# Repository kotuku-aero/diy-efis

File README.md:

# CanFly Avionics SDK

Open-source SDK for developing custom avionics applications for experimental aircraft. Build once, run on Windows for development and deploy to embedded MIPS32 hardware.

## Table of Contents

- [System Overview](#system-overview)
- [Dual Development Architecture](#dual-development-architecture)
- [Prerequisites](#prerequisites)
- [Quick Start](#quick-start)
- [Project Structure](#project-structure)
- [Building Applications](#building-applications)
  - [Windows Development Build](#windows-development-build)
  - [MIPS32 Embedded Build](#mips32-embedded-build)
- [Application Packaging](#application-packaging)
- [CLion IDE Setup](#clion-ide-setup)
- [Creating Your Own Application](#creating-your-own-application)
- [Troubleshooting](#troubleshooting)

## System Overview

The CanFly SDK provides a complete framework for building glass cockpit avionics applications that run on both Windows (for development/testing) and embedded MIPS32 hardware (for deployment).

**Key Features:**
- **Dual-target compilation:** Same codebase runs on Windows and MIPS32 embedded systems
- **User-mode architecture:** Applications run in protected user space with kernel syscalls
- **Proton UI framework:** XML-based layout system with automatic code generation
- **CanFly syscalls:** Hardware abstraction for CAN bus, sensors, displays, and I/O
- **Automatic packaging:** Post-build packaging creates deployable binary images with SHA256 integrity

## Dual Development Architecture

CanFly applications use a unique dual-target architecture:

### Windows Development Build (MSVC/MinGW)

- **Purpose:** Rapid UI development, testing, and debugging on PC
- **Platform:** Windows 10/11 with Visual Studio or MinGW
- **Libraries:** `w32_canfly.dll` - Windows emulation of CanFly kernel syscalls
- **Output:** Windows executable (`.exe`)
- **Use case:**
  - Develop and test UI layouts
  - Debug application logic
  - Iterate quickly without hardware

### MIPS32 Embedded Build (mips32r2-elf-gcc)

- **Purpose:** Deployment to embedded avionics hardware
- **Platform:** MIPS32 processor running CanFly kernel
- **Libraries:** `canfly` - User-mode syscall stubs
- **Output:**
  - ELF executable (`.elf`) for debugging
  - Packaged binary (`.bin`) with header and SHA256 for deployment
- **Architecture:** User-mode applications running at 0x00000020 in 384KB RAM
- **Use case:**
  - Final deployment to aircraft hardware
  - Hardware integration testing
  - Performance validation

### How It Works

1. **Write once:** Your application code is identical for both targets
2. **Conditional compilation:** `#ifdef MIPS32_BUILD` for platform-specific code
3. **Common syscalls:** CanFly API is the same on both platforms
4. **Build twice:**
   - Windows build for development
   - MIPS32 build for deployment

## Prerequisites

### For Windows Development (Required)

**Recommended IDE:**
- **CLion** (free for non-commercial use): https://www.jetbrains.com/clion/
  - Excellent CMake integration
  - Cross-platform debugging
  - Built-in code analysis

**Build Tools (choose one):**

**Option 1: Visual Studio 2022 Build Tools** (recommended)
```powershell
# Run as Administrator
winget install Microsoft.VisualStudio.2022.BuildTools --force --override "--passive --wait --add Microsoft.VisualStudio.Workload.VCTools;includeRecommended"
```

**Option 2: MinGW-w32** (alternative)
```powershell
winget install mingw-w32
```

**Additional Tools:**
- CMake 3.15+ (bundled with CLion)
- Git with submodules support
- Python 3.8+ (for build tools and packaging)

### For MIPS32 Embedded Development (Required)

**MIPS32 Compiler Toolchain:**
- Download from: https://github.com/kotuku-aero/mips32
- Extract to: `C:\pic32\` (or update toolchain file path)
- Adds: `mips32r2-elf-gcc`, `mips32r2-elf-ld`, `mips32r2-elf-size`, `mips32r2-elf-gdb`

**Python Libraries:**
```bash
pip install pyelftools
```

### Not Supported

**XC32 Compiler:** While the codebase can build with XC32, we do not officially support it. Use the free mips32r2-elf-gcc toolchain instead.

## Quick Start

### 1. Clone the Repository

```bash
git clone --recurse-submodules https://github.com/kotuku-aero/canfly.git
cd canfly/diy-efis
```

### 2. Build Example Application (Windows)

```bash
cd apps/att_au_nz
mkdir build-win
cd build-win
cmake ..
cmake --build . --config Release

# Run the application
./bin/Release/att_au_nz.exe -x 1024 -y 768
```

### 3. Build for MIPS32 Hardware

```bash
cd apps/att_au_nz
mkdir build-mips32
cd build-mips32
cmake -DCMAKE_TOOLCHAIN_FILE=../../cmake/pic32-mips32r2-toolchain.cmake ..
cmake --build .

# Outputs:
# - firmware/att_au_nz.elf (for debugging)
# - images/att_au_nz.bin (for deployment)
```

## Project Structure

```
diy-efis/
├── apps/                      # User applications
│   ├── att_au_nz/            # Example: Attitude indicator (AU/NZ regs)
│   │   ├── main.c            # Application entry point
│   │   ├── att.c             # Attitude display logic
│   │   ├── layout/           # XML UI layouts
│   │   └── CMakeLists.txt
│   └── [your_app]/           # Your custom application
|
├── bin/                      # binary files
|   ├── CanFly.Commander.exe  # CanFly application manager
|   └── msh.exe               # gdb server for canfly hardware.
│
├── src/                      # SDK source code
│   ├── canfly/               # User-mode kernel interface
│   │   ├── canfly_stubs.c    # Syscall stubs (generated)
│   │   ├── newlib_stubs.c    # Minimal C library support
│   │   ├── crt0.S            # User-mode startup code
│   │   └── canfly_app.ld     # Linker script (384KB user RAM)
│   ├── mfdlib/               # Display/UI library
│   └── proton/               # UI framework & XML processing
|
├── tools/                    # Development tools
|   └── yehudi                # XML layout code generator
│
├── lib/                      # Platform abstraction
│   ├── libw32_canfly.so      # linux version (for development)
|   └── w32_canfly.dll/lib    # Windows DLL export definitions
│
├── cmake/                    # Build system
│   ├── MFDCommon.cmake       # Shared build configuration
│   └── mips32-toolchain.cmake
│
├── scripts/                  # Build tools
│   └── package_usermode.py   # Binary packaging tool
│
└── include/                  # SDK headers
    ├── canfly_api.md         # API documentation
    ├── canfly_types.h        # Common types
    ├── CanFlyID.def          # Definitions of the published CAN IDs
    ├── canfly.h              # Main CanFly API
    └── sys_canfly.h          # Syscall definitions
```

## Building Applications

### Windows Development Build

Used for rapid development and testing without hardware.

**From CLion:**
1. Open `diy-efis` as project
2. Select **Windows-Release** profile
3. Build → Build Project (Ctrl+F9)
4. Run → Run (Shift+F10)

**From Command Line:**
```bash
cd apps/att_au_nz
cmake -B build-win -DCMAKE_BUILD_TYPE=Release
cmake --build build-win --config Release

# Run with custom window size
./build-win/bin/Release/att_au_nz.exe -x 1024 -y 768
```

**Debug Build:**
```bash
cmake -B build-win-debug -DCMAKE_BUILD_TYPE=Debug
cmake --build build-win-debug --config Debug
```

### MIPS32 Embedded Build

Used for deployment to avionics hardware.

**From CLion:**
1. Select **MIPS32-Release** profile
2. Build → Build Project (Ctrl+F9)
3. Output:
   - `cmake-build-mips32-release/firmware/att_au_nz.elf`
   - `cmake-build-mips32-release/images/att_au_nz.bin`

**From Command Line:**
```bash
cd apps/att_au_nz
cmake -B build-mips32 \
  -DCMAKE_TOOLCHAIN_FILE=../../cmake/pic32-mips32r2-toolchain.cmake \
  -DCMAKE_BUILD_TYPE=Release
cmake --build build-mips32

# View program size
mips32r2-elf-size build-mips32/firmware/att_au_nz.elf
```

**Build Output:**
```
firmware/att_au_nz.elf    # ELF file with debug symbols
images/att_au_nz.bin      # Packaged binary for deployment
```

## Application Packaging

MIPS32 builds automatically package the ELF into a deployable binary format.

### Package Format

```
[32-byte header]
  - 0x10000008: Branch instruction (skip header)
  - 0x00000c00: EHB (execution hazard barrier)
  - Image length (big-endian)
  - Reserved
  - Image name (16 bytes)

[Application binary]
  - Code and data sections from ELF
  - 32-byte aligned

[SHA256 signature]
  - "sig-sha256" (28 bytes)
  - Hash length: 32 (big-endian)
  - SHA256 hash of header + binary
  - Padding to 32-byte alignment
```

### Manual Packaging

```bash
python3 scripts/package_usermode.py \
  -e firmware/att_au_nz.elf \
  -o images \
  -n att_au_nz
```

### Deployment

Upload the `.bin` file to the CanFly device using the Commander tool:
1. Open Commander (.NET tool)
2. File Explorer → Upload
3. Select `att_au_nz.bin`
4. Device loads and verifies SHA256
5. Application runs in user-mode at 0x00000020

Keep the `.elf` file for debugging with GDB/JTAG.

## CLion IDE Setup

CLion is the recommended IDE for CanFly development.

### Install CLion

Download from: https://www.jetbrains.com/clion/

**Free License Options:**
- Educational license (students/teachers)
- Open source project license
- 30-day trial

### CMake Profiles

Create these profiles in: **Settings → Build, Execution, Deployment → CMake**

#### Profile: Windows-Debug
```
Name: Windows-Debug
Build type: Debug
Toolchain: Visual Studio (or MinGW)
CMake options: (leave empty)
Build directory: cmake-build-debug
```

#### Profile: Windows-Release
```
Name: Windows-Release
Build type: Release
Toolchain: Visual Studio (or MinGW)
CMake options: (leave empty)
Build directory: cmake-build-release
```

#### Profile: MIPS32-Debug
```
Name: MIPS32-Debug
Build type: Debug
Toolchain: Visual Studio (placeholder - actual toolchain from file)
CMake options: -DCMAKE_TOOLCHAIN_FILE=cmake/pic32-mips32r2-toolchain.cmake
Build directory: cmake-build-mips32-debug
```

#### Profile: MIPS32-Release
```
Name: MIPS32-Release
Build type: Release
Toolchain: Visual Studio (placeholder - actual toolchain from file)
CMake options: -DCMAKE_TOOLCHAIN_FILE=cmake/pic32-mips32r2-toolchain.cmake
Build directory: cmake-build-mips32-release
```

### Building in CLion

1. **Select Profile:** Bottom toolbar → Profile dropdown
2. **Build All:** Hammer icon or Ctrl+F9
3. **Build Target:** Right-click target → Build
4. **Clean:** Build → Clean
5. **Reload CMake:** Tools → CMake → Reload CMake Project

### Debugging

**Windows Builds:**
- Set breakpoints in source
- Select Windows-Debug profile
- Run → Debug (Shift+F9)
- Full debugging support

**MIPS32 Builds:**
- Use `.elf` file with GDB
- Create an Embedded debug target in CLion
- CLion will download the application into the device and start debugging

## Creating Your Own Application

### 1. Create Application Directory

```bash
cd diy-efis/apps
mkdir my_avionics
cd my_avionics
```

### 2. Create CMakeLists.txt

```cmake
cmake_minimum_required(VERSION 3.15)
project(my_avionics C)

# Include common configuration
include(${CMAKE_CURRENT_SOURCE_DIR}/../../cmake/MFDCommon.cmake)

# Source files
set(SOURCES
    main.c
    my_logic.c
)

# Platform-specific build
if(MIPS32_BUILD)
    # MIPS32 embedded build
    add_executable(my_avionics ${SOURCES})

    mfd_configure_pic32_target(
        TARGET my_avionics
    )
else()
    # Windows development build
    add_executable(my_avionics ${SOURCES})

    mfd_configure_win32_target(
        TARGET my_avionics
    )
endif()
```

### 3. Create main.c

```c
#include "canfly.h"

#ifndef MIPS32_BUILD
// Windows debug arguments
int main(int argc, char** argv)
  {
  if (failed(canfly_init(argc, argv)))
    return -1;
#else
// MIPS32 user-mode (no arguments)
int main()
  {
#endif

  // Your application logic here

  return 0;
  }
```

### 4. Build and Test

```bash
# Windows build
cmake -B build-win
cmake --build build-win

# MIPS32 build
cmake -B build-mips32 \
  -DCMAKE_TOOLCHAIN_FILE=../../cmake/pic32-mips32r2-toolchain.cmake
cmake --build build-mips32
```

## Troubleshooting

### MIPS32 Compiler Not Found

**Error:** `CMAKE_C_COMPILER not found`

**Solution:**
```bash
# Verify installation
C:\pic32\bin\mips32r2-elf-gcc.exe --version

# Update toolchain file if installed elsewhere
# Edit: cmake/pic32-mips32r2-toolchain.cmake
set(MIPS32_TOOLCHAIN_PATH "C:/your/path/here")
```

### Missing Python Dependencies

**Error:** `ModuleNotFoundError: No module named 'elftools'`

**Solution:**
```bash
pip install pyelftools
```

### Linker Errors: Undefined Reference to Syscalls

**Error:** `undefined reference to 'cfg_open_key'`

**Solution:**
- Ensure `canfly` library is linked (should be automatic via `MFDCommon.cmake`)
- Check link order in `mfd_configure_pic32_target()`
- Verify syscall stubs are generated: `diy-efis/src/canfly/canfly_stubs.c`

### Entry Point Not Found

**Error:** `warning: cannot find entry symbol _reset`

**Solution:**
- Ensure `crt0.S` is in `canfly` library sources
- Verify CMake project includes ASM language: `project(canfly LANGUAGES C ASM)`
- Check linker script: `canfly_app.ld` defines `ENTRY(_reset)`

### Program Size Too Small (24 bytes)

**Issue:** Binary is suspiciously small, likely missing code

**Solution:**
- Check that `canfly` library links before `gcc` in link order
- Verify all source files are in `add_executable()` or linked libraries
- Look for undefined symbols in build output

### CLion Shows Red Underlines

**Issue:** Code appears to have errors but builds successfully

**Solution:**
1. Tools → CMake → Reset Cache and Reload Project
2. Ensure correct CMake profile is selected
3. File → Invalidate Caches → Invalidate and Restart

### Windows Build Can't Find w32_canfly.lib

**Error:** `Cannot find w32_canfly.lib`

**Solution:**
- Ensure submodules are initialized: `git submodule update --init --recursive`
- Check that `libs/w32_canfly/` exists and contains the library
- Verify path in `mfd_configure_win32_target()` function

## Additional Resources

- **CanFly Kernel Documentation:** [Coming soon]
- **Proton UI Framework Guide:** See `src/proton/README.md`
- **MIPS32 Toolchain:** https://github.com/kotuku-aero/mips32r2-elf-gcc
- **CMake Documentation:** https://cmake.org/documentation/
- **CLion CMake Support:** https://www.jetbrains.com/help/clion/cmake-support.html

## Contributing

Contributions are welcome! Please:
1. Fork the repository
2. Create a feature branch
3. Test on both Windows and MIPS32
4. Submit a pull request

## License

[Your license here]

## Support

For questions or issues:
- GitHub Issues: https://github.com/kotuku-aero/canfly/issues
- Email: support@kotuku.aero
- Forum: [Coming soon]

---

**Happy flying with CanFly!** ✈️

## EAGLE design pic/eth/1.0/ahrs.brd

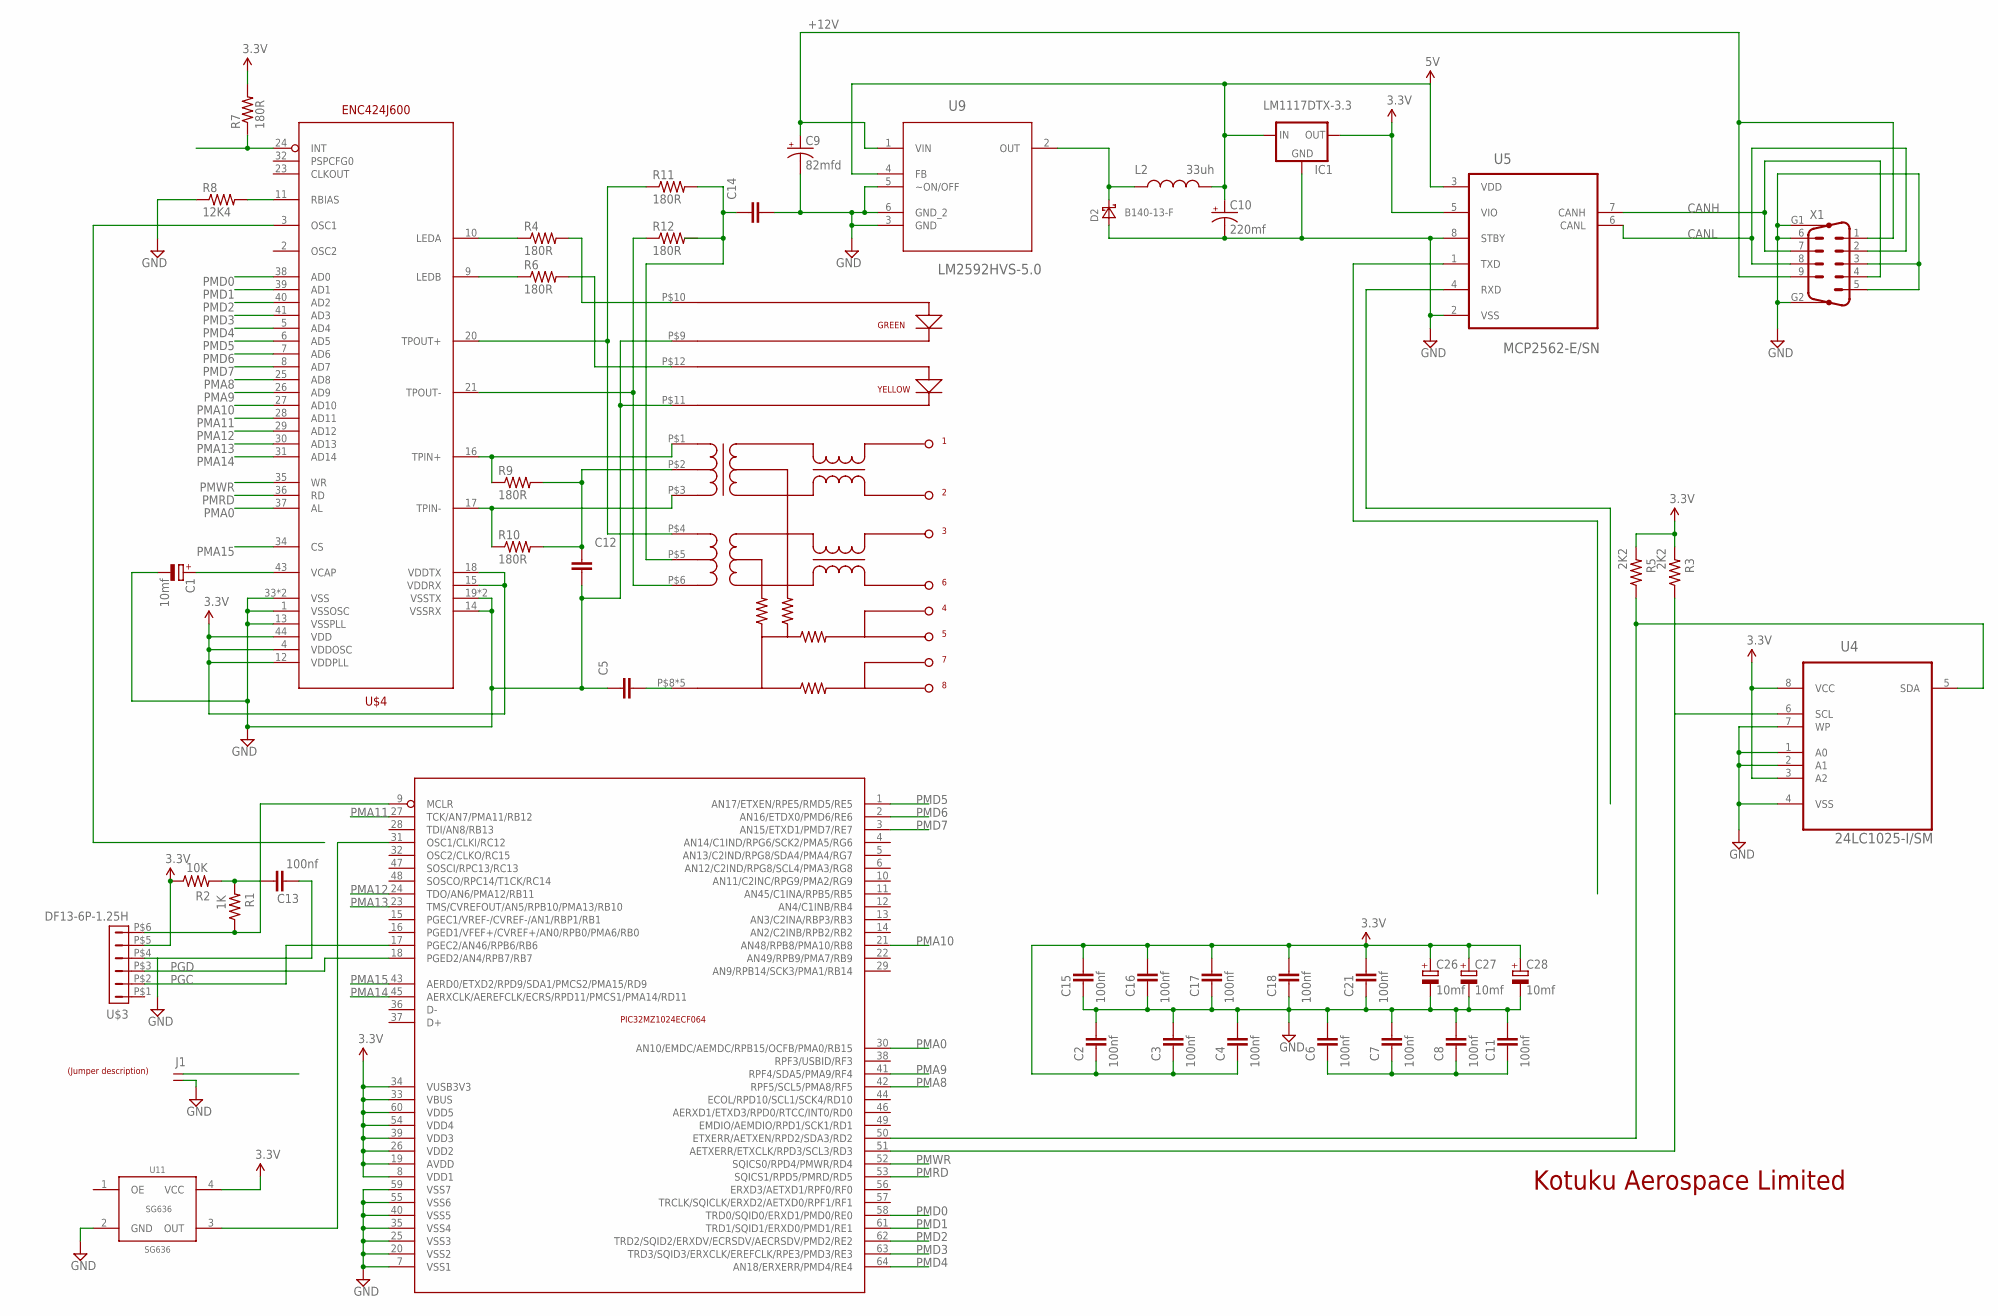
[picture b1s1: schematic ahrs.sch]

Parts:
C1, C26, C27, C28: 10mf; SMC_A
C2, C3, C4, C6, C7, C8, C11, C13, C15, C16, C17, C18, C21: 100nf; C805
C5: CAPACITOR_NPOL-1206; C1206
C9: 82mfd; SVPF-E7
C10: 220mf; EIA7343
C12, C14: CAPACITOR_NPOL-0603; C603
D2: B140-13-F; SMA
IC1: LM1117DTX-3.3; TO252
J1: JUMPER-1X2
L2: 33uh; 1812
R1: 1K; 0603-RES; PARTNO ERJ-3GEYJ103V
R2: 10K; 0603-RES; PARTNO ERJ-3GEYJ103V
R3, R5: 2K2; 0603-RES; PARTNO ERJ-3GEYJ103V
R4, R6, R7, R9, R10, R11, R12: 180R; 0603-RES
R8: 12K4; 0603-RES
U4: 24LC1025-I/SM; SOIC8-N_MC
U5: MCP2562-E/SN; SOIC-8N
U9: LM2592HVS-5.0; TO170P1435X457-5N
U11: SG636; PARTNO SG-636PCE 10.000MHZ
U$1: LABEL_JUMPER_1X2; JUMP2_DESC
U$2: PIC32MZ1024; TQFP-64
U$3: DF13-6P-1.25H; DF13A-6P-1.25H
U$4: ENC424J600; TQFP44
U$5: J1B1211CCD
X1: M09HP

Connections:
3.3V: C2.2, C3.2, C4.2, C15.1, C16.1, C17.1, C18.1, C21.1, C26.+, C27.+, C28.+, IC1.TAB (OUT), R2.1, R3.2, R5.2, R7.2, U4.3 (A2), U4.8 (VCC), U5.5 (VIO), U11.4 (VCC), U$2.8 (VDD1), U$2.19 (AVDD), U$2.26 (VDD2), U$2.33 (VBUS), U$2.34 (VUSB3V3), U$2.39 (VDD3), U$2.54 (VDD4), U$2.60 (VDD5), U$3.P$5 (5), U$4.4 (VDDOSC), U$4.12 (VDDPLL), U$4.15 (VDDRX), U$4.18 (VDDTX), U$4.44 (VDD)
5V: C10.A (+), IC1.2 (IN), L2.2, U5.3 (VDD), U9.4 (FB)
!MCLR: R1.1, U$2.9 (MCLR), U$3.P$6 (6)
+12V: C9.P$2 (+), U9.1 (VIN), X1.1, X1.9
CANH: U5.7 (CANH), X1.4, X1.7
CANL: U5.6 (CANL), X1.2, X1.8
GND: C1.-, C2.1, C3.1, C4.1, C5.1, C6.1, C7.1, C8.1, C9.P$1 (-), C10.C (-), C11.1, C12.2, C13.2, C14.2, C15.2, C16.2, C17.2, C18.2, C21.2, C26.-, C27.-, C28.-, D2.A, IC1.1 (GND), J1.2, R8.1, U4.1 (A0), U4.2 (A1), U4.4 (VSS), U4.7 (WP), U5.2 (VSS), U5.8 (STBY), U9.3 (GND), U9.5 (~ON/OFF), U9.6 (GND_2), U11.2 (GND), U$2.7 (VSS1), U$2.20 (VSS2), U$2.25 (VSS3), U$2.35 (VSS4), U$2.40 (VSS5), U$2.55 (VSS6), U$2.59 (VSS7), U$3.P$4 (4), U$4.1 (VSSOSC), U$4.13 (VSSPLL), U$4.14 (VSSRX), U$4.19 (VSSTX), U$4.22 (VSSTX), U$4.33 (VSS), U$4.42 (VSS), U$5.P$9 (GREEN_K), U$5.P$11 (YELLOW_K), X1.3, X1.5, X1.6, X1.G1, X1.G2
unnamed: R11.1, U$4.20 (TPOUT+), U$5.P$4 (RX+)
unnamed: R12.1, U$4.21 (TPOUT-), U$5.P$6 (RX-)
unnamed: R9.1, U$4.16 (TPIN+), U$5.P$1 (TX+)
unnamed: C13.1, R1.2, R2.2
unnamed: R10.1, U$4.17 (TPIN-), U$5.P$3 (TX-)
unnamed: U11.3 (OUT), U$2.31 (OSC1/CLKI/RC12)
unnamed: C6.2, C7.2, C8.2, C11.2
unnamed: R4.1, U$4.10 (LEDA)
unnamed: R4.2, U$5.P$10 (GREEN_A)
unnamed: D2.C, L2.1, U9.2 (OUT)
unnamed: R6.2, U$5.P$12 (YELLOW_A)
unnamed: R6.1, U$4.9 (LEDB)
unnamed: R7.1, U$4.24 (INT)
unnamed: R8.2, U$4.11 (RBIAS)
unnamed: C5.2, U$5.P$8 (GNDIN), U$5.P$13 (GNDIN), U$5.P$14 (GNDIN), U$5.P$15 (GNDIN), U$5.P$16 (GNDIN)
unnamed: C1.+, U$4.43 (VCAP)
unnamed: C12.1, R9.2, R10.2, U$5.P$2 (P2IN)
unnamed: C14.1, R11.2, U$5.P$5 (P5IN)
PGC: U$2.17 (PGEC2/AN46/RPB6/RB6), U$3.P$2 (2)
PGD: U$2.18 (PGED2/AN4/RPB7/RB7), U$3.P$3 (3)
PMA0: U$2.30 (AN10/EMDC/AEMDC/RPB15/OCFB/PMA0/RB15), U$4.37 (AL)
PMA8: U$2.42 (RPF5/SCL5/PMA8/RF5), U$4.25 (AD8)
PMA9: U$2.41 (RPF4/SDA5/PMA9/RF4), U$4.26 (AD9)
PMA10: U$2.21 (AN48/RPB8/PMA10/RB8), U$4.27 (AD10)
PMA11: U$2.27 (TCK/AN7/PMA11/RB12), U$4.28 (AD11)
PMA12: U$2.24 (TDO/AN6/PMA12/RB11), U$4.29 (AD12)
PMA13: U$2.23 (TMS/CVREFOUT/AN5/RPB10/PMA13/RB10), U$4.30 (AD13)
PMA14: U$2.45 (AERXCLK/AEREFCLK/ECRS/RPD11/PMCS1/PMA14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), U$4.31 (AD14)
PMA15: U$2.43 (AERD0/ETXD2/RPD9/SDA1/PMCS2/PMA15/RD9), U$4.34 (CS)
PMD0: U$2.58 (TRD0/SQID0/ERXD1/PMD0/RE0), U$4.38 (AD0)
PMD1: U$2.61 (TRD1/SQID1/ERXD0/PMD1/RE1), U$4.39 (AD1)
PMD2: U$2.62 (TRD2/SQID2/ERXDV/ECRSDV/AECRSDV/PMD2/RE2), U$4.40 (AD2)
PMD3: U$2.63 (TRD3/SQID3/ERXCLK/EREFCLK/RPE3/PMD3/RE3), U$4.41 (AD3)
PMD4: U$2.64 (AN18/ERXERR/PMD4/RE4), U$4.5 (AD4)
PMD5: U$2.1 (AN17/ETXEN/RPE5/RMD5/RE5), U$4.6 (AD5)
PMD6: U$2.2 (AN16/ETDX0/PMD6/RE6), U$4.7 (AD6)
PMD7: U$2.3 (AN15/ETXD1/PMD7/RE7), U$4.8 (AD7)
PMRD: U$2.53 (SQICS1/RPD5/PMRD/RD5), U$4.36 (RD)
PMWR: U$2.52 (SQICS0/RPD4/PMWR/RD4), U$4.35 (WR)
SCL: R3.1, U4.6 (SCL), U$2.51 (AETXERR/ETXCLK/RPD3/SCL3/RD3)
SDA: R5.1, U4.5 (SDA), U$2.50 (ETXERR/AETXEN/RPD2/SDA3/RD2)

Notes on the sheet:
Kotuku Aerospace Limited

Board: 2 copper layers, 48 parts (0 on the bottom side), 48 nets, no tracks yet.

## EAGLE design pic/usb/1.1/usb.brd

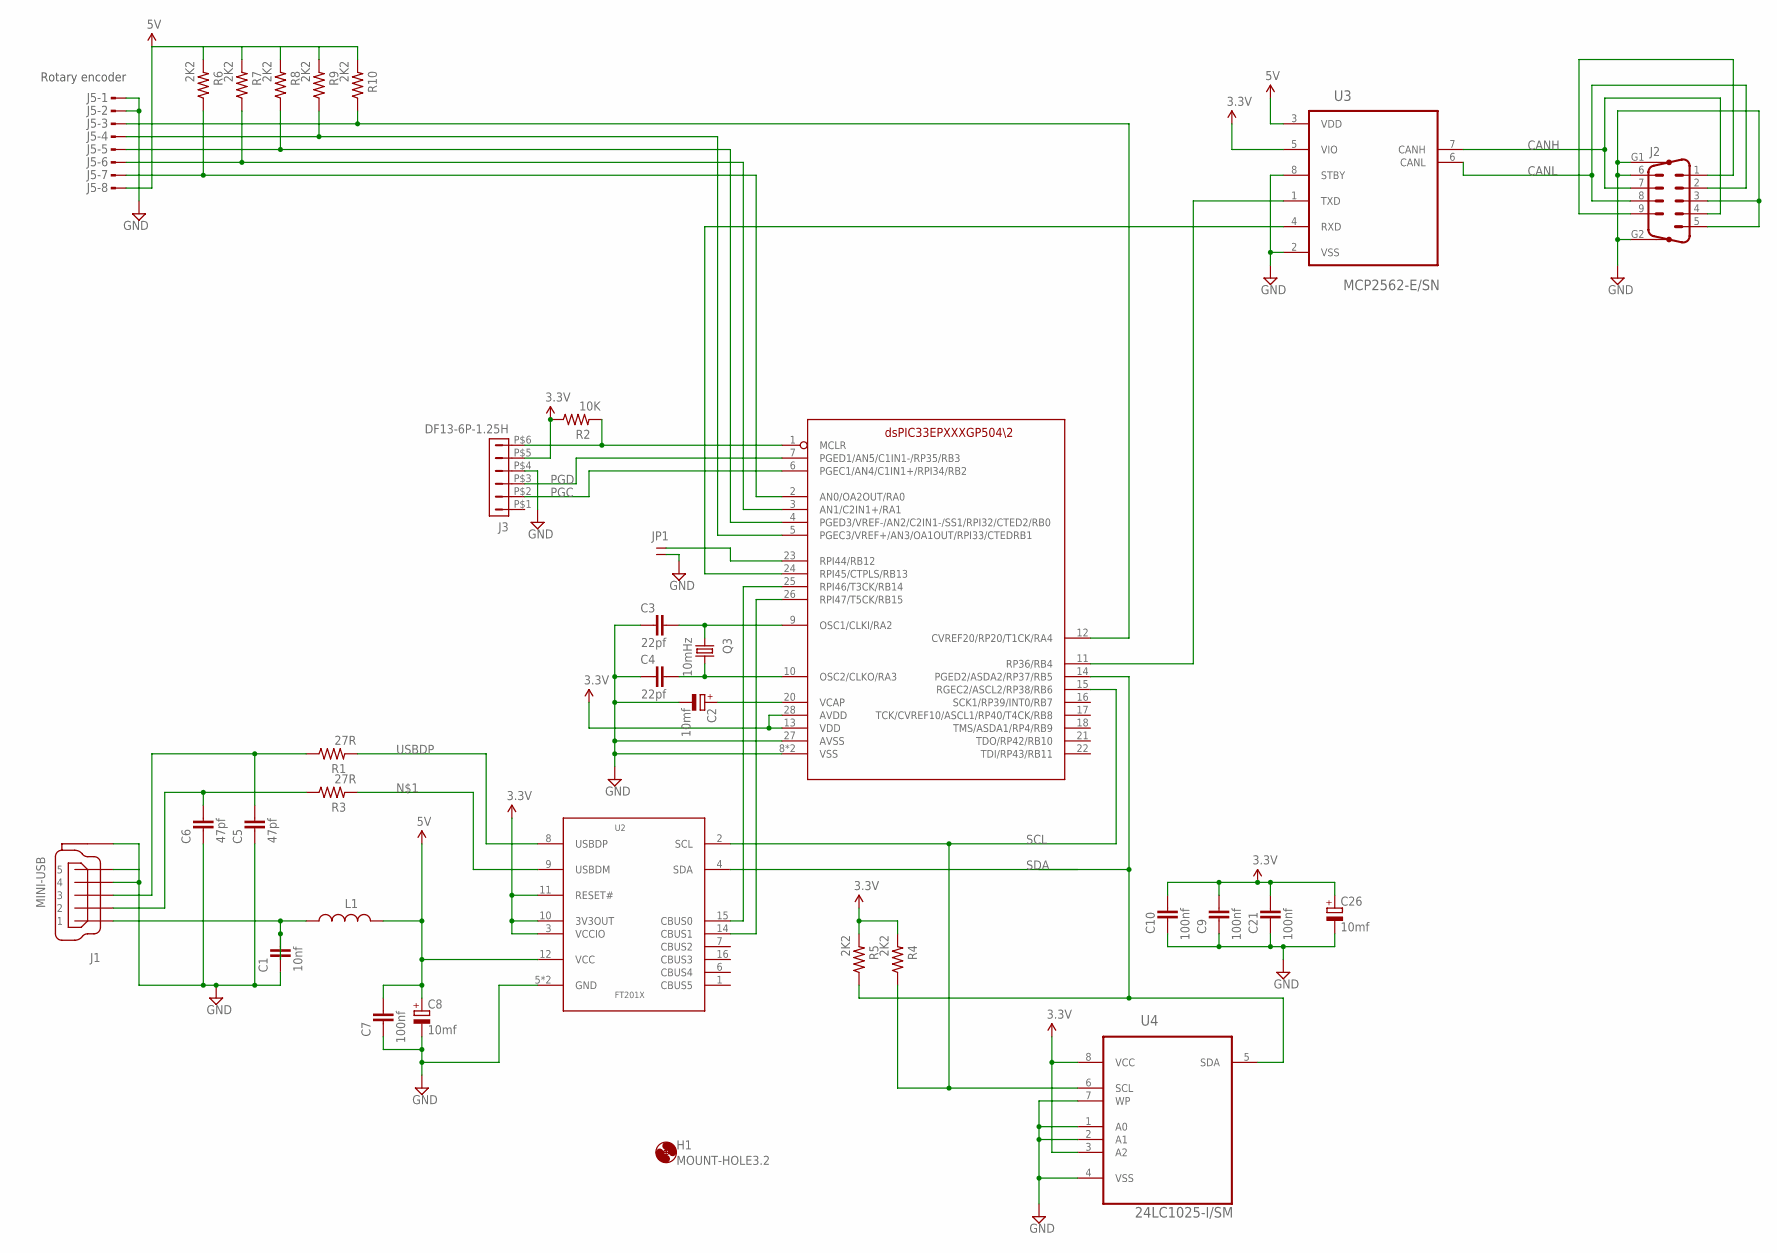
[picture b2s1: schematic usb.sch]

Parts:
C1: 10nf; C805
C2, C8, C26: 10mf; SMC_A
C3, C4: 22pf; C805
C5, C6: 47pf; C805
C7, C9, C10, C21: 100nf; C805
H1: MOUNT-HOLE3.2; 3,2
J1: MINI-USB
J2: M09HP
J3: DF13-6P-1.25H; DF13A-6P-1.25H
J5: MTOP-8; PARTNO 7-215079-8
JP1: JUMPER-1X2
L1: FERRITE-0603; FB603
Q3: 10mHz; HC49/S; PARTNO 9B-10.000MBBK-B
R1, R3: 27R; 0603-RES; PARTNO ERJ-3GEYJ103V
R2: 10K; 0603-RES; PARTNO ERJ-3GEYJ103V
R4, R5: 2K2; 0603-RES; PARTNO ERJ-3GEYJ103V
R6, R7, R8, R9, R10: 2K2; 0603-RES; PARTNO RC0603FR-072K2L
U1: DSPIC33EPXXXGP502; SOIC-28
U2: FT201X; TSSOP-16
U3: MCP2562-E/SN; SOIC-8N
U4: 24LC1025-I/SM; SOIC8-N_MC

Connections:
3.3V: C9.1, C10.1, C21.1, C26.+, J3.P$5 (5), R2.1, R4.2, R5.2, U1.13 (VDD), U1.28 (AVDD), U2.3 (VCCIO), U2.10 (3V3OUT), U2.11 (RESET#), U3.5 (VIO), U4.3 (A2), U4.8 (VCC)
5V: C7.1, C8.+, J5.8, L1.2, R6.2, R7.2, R8.2, R9.2, R10.2, U2.12 (VCC), U3.3 (VDD)
!MCLR: J3.P$6 (6), R2.2, U1.1 (MCLR)
+12V: J2.1, J2.9
A+: J5.7, R6.1, U1.2 (AN0/OA2OUT/RA0)
A-: J5.6, R7.1, U1.3 (AN1/C2IN1+/RA1)
B+: J5.5, R8.1, U1.4 (PGED3/VREF-/AN2/C2IN1-/SS1/RPI32/CTED2/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)
B-: J5.4, R9.1, U1.5 (PGEC3/VREF+/AN3/OA1OUT/RPI33/CTEDRB1)
CANH: J2.4, J2.7, U3.7 (CANH)
CANL: J2.2, J2.8, U3.6 (CANL)
GND: C1.2, C2.-, C3.2, C4.2, C5.2, C6.2, C7.2, C8.-, C9.2, C10.2, C21.2, C26.-, J1.4, J1.5, J1.M1 (MOUNT), J1.M2 (MOUNT), J1.M3 (MOUNT), J1.M4 (MOUNT), J2.3, J2.5, J2.6, J2.G1, J2.G2, J3.P$4 (4), J5.1, J5.2, JP1.2, U1.8 (VSS), U1.19 (VSS), U1.27 (AVSS), U2.5 (GND), U2.13 (GND), U3.2 (VSS), U3.8 (STBY), U4.1 (A0), U4.2 (A1), U4.4 (VSS), U4.7 (WP)
unnamed: R3.2, U2.9 (USBDM)
unnamed: U1.25 (RPI46/T3CK/RB14), U2.15 (CBUS0)
unnamed: U1.24 (RPI45/CTPLS/RB13), U3.4 (RXD)
unnamed: C2.+, U1.20 (VCAP)
unnamed: C3.1, Q3.2, U1.9 (OSC1/CLKI/RA2)
unnamed: U1.11 (RP36/RB4), U3.1 (TXD)
unnamed: U1.26 (RPI47/T5CK/RB15), U2.14 (CBUS1)
unnamed: C6.1, J1.2, R3.1
unnamed: C1.1, J1.1, L1.1
unnamed: C5.1, J1.3, R1.1
unnamed: JP1.1, U1.23 (RPI44/RB12)
unnamed: C4.1, Q3.1, U1.10 (OSC2/CLKO/RA3)
PGC: J3.P$2 (2), U1.6 (PGEC1/AN4/C1IN1+/RPI34/RB2)
PGD: J3.P$3 (3), U1.7 (PGED1/AN5/C1IN1-/RP35/RB3)
SCL: R4.1, U1.15 (RGEC2/ASCL2/RP38/RB6), U2.2 (SCL), U4.6 (SCL)
SDA: R5.1, U1.14 (PGED2/ASDA2/RP37/RB5), U2.4 (SDA), U4.5 (SDA)
SW1: J5.3, R10.1, U1.12 (CVREF20/RP20/T1CK/RA4)
USBDP: R1.2, U2.8 (USBDP)

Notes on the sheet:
Rotary encoder

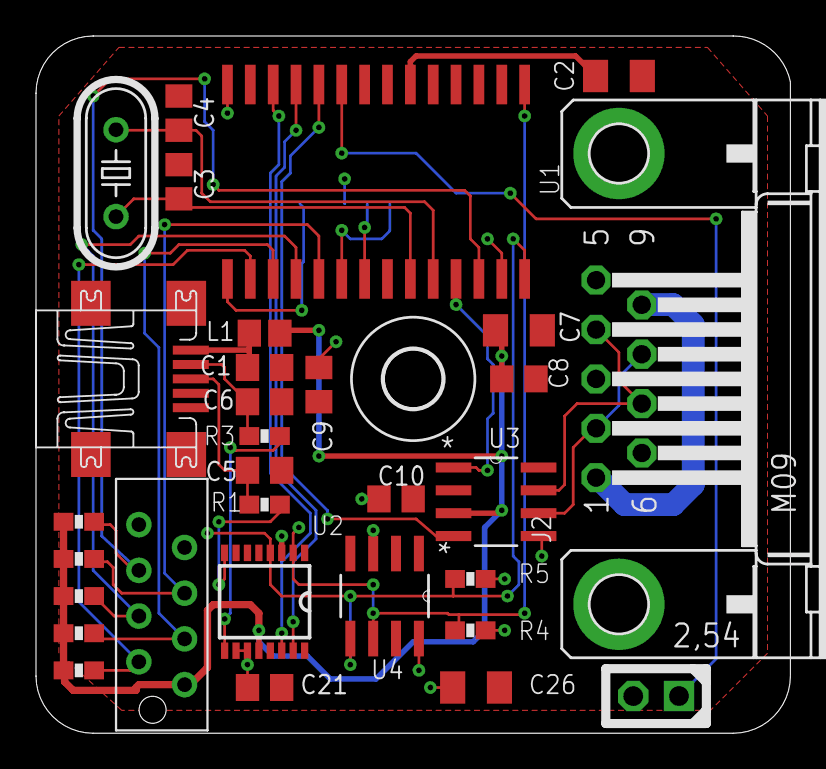
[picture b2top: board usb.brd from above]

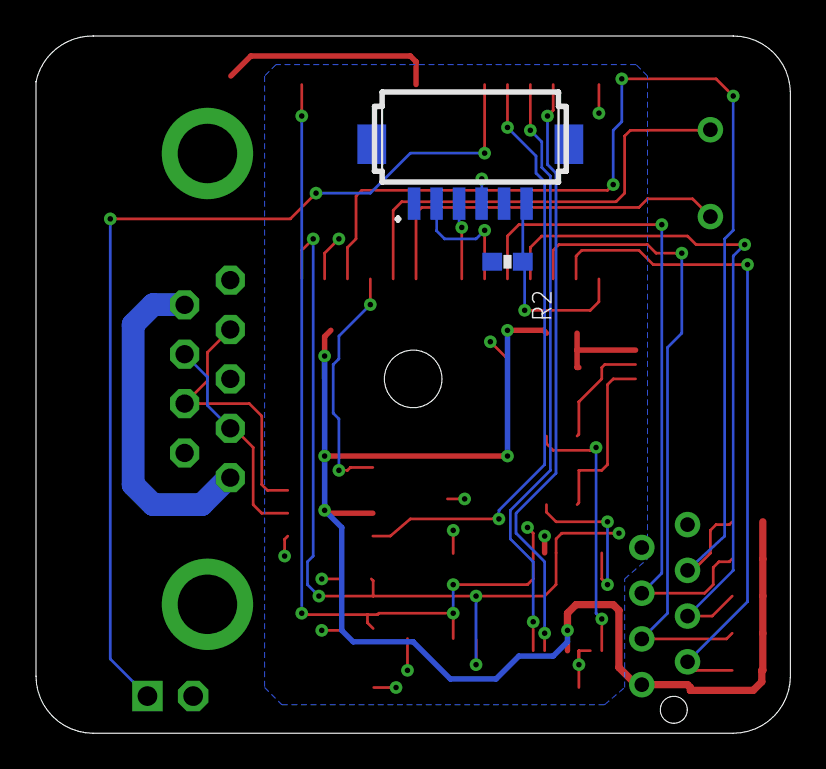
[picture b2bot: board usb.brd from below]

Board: 2 copper layers, 41.9 x 38.7 mm, 34 parts (2 on the bottom side), 29 nets.

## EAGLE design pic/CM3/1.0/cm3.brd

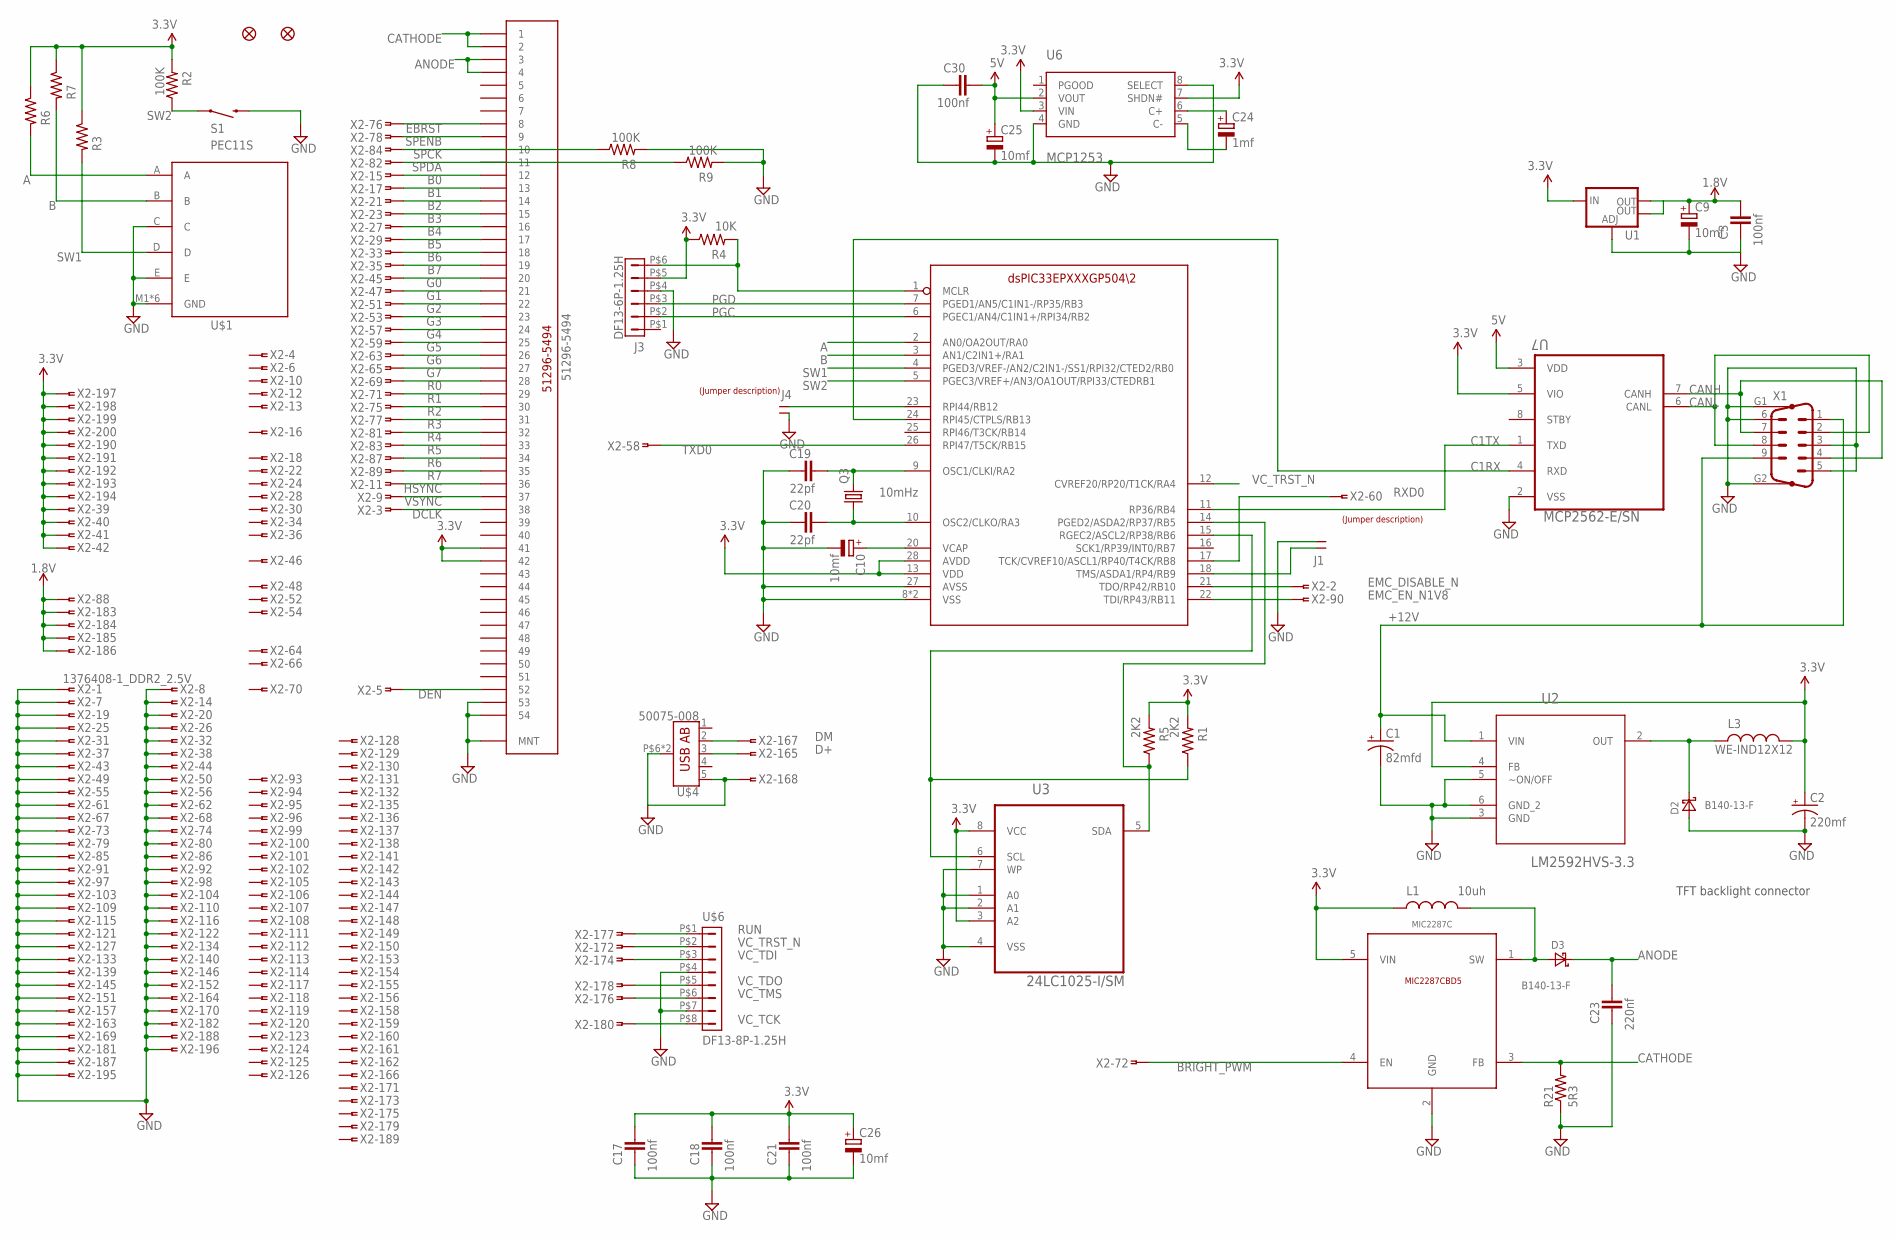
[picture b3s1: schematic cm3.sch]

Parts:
C1: 82mfd; SVPF-E7
C2: 220mf; EIA7343; PARTNO T545X227M016ATE035
C3, C17, C18, C21, C30: 100nf; C805; PARTNO CL21F104ZBCNNNC
C9, C10, C25, C26: 10mf; SMC_A; PARTNO T491A106K004AT
C19, C20: 22pf; C805; PARTNO C0805C220J5GACTU
C23: 220nf; C805; PARTNO CL21F224ZBCNNNC
C24: 1mf; SMC_A; PARTNO F931C105MAA
D2, D3: B140-13-F; SMA; PARTNO B140-13-F
J1, J4: JUMPER-1X2; PARTNO M20-9770246
J3: DF13-6P-1.25H; DF13A-6P-1.25H; PARTNO DF13A-6P-1.25H(20)
JP1, JP2: FIDUCIAL1.5X3; FIDUCIAL-1.5X3
L1: 10uh; 1812; PARTNO VLF504015MT-100M
L3: WE-IND12X12; IND12X12
Q3: 10mHz; HC49/S; PARTNO ATS100B-E
R1, R5: 2K2; 0603-RES; PARTNO RC0603FR-072K2L
R2, R8, R9: 100K; 0603-RES; PARTNO RC0603JR-07100KL
R3, R4, R6, R7: 10K; 0603-RES; PARTNO RC0603FR-0710KL
R21: 5R3; 1812; PARTNO RL1218FK-070R604L
S1: SWITCH-MOMENTARY-2SMD-4; TACTILE_SWITCH_TALL; PARTNO MJTP1138BTR
U1: V_REG_LM1117SOT223; SOT223
U2: LM2592HVS-3.3; TO170P1435X457-5N
U3: 24LC1025-I/SM; SOIC8-N_MC; PARTNO 24LC1025T-I/SN
U5: DSPIC33EPXXXGP502; SOIC-28
U6: MCP1253; MSOP8; PARTNO MCP1253-33X50I/MS
U7: MCP2562-E/SN; SOIC-8N; PARTNO MCP2562-E/SN
U9: MIC2287C; SOT-23-5; PARTNO MIC2287CYD5-TR
U$1: PEC11S; PARTNO PEC11S-9215K-H0015
U$2: 51296-5494; PARTNO 51296-5494
U$3, U$5: LABEL_JUMPER_1X2; JUMP2_DESC
U$4: 50075-008; 500075-008
U$6: DF13-8P-1.25H; DF13A-8P-1.25H
X1: M09VP
X2: 1376408-1_DDR2_2.5V; 6-1376408-1

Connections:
1.8V: C3.1, C9.+, U1.2 (OUT), U1.4 (OUT), X2.88, X2.183, X2.184, X2.185, X2.186
3.3V: C2.A (+), C17.1, C18.1, C21.1, C26.+, J3.P$5 (5), L1.1, L3.P$2 (2), R1.2, R2.2, R3.1, R4.1, R5.2, R6.1, R7.1, U1.3 (IN), U2.4 (FB), U3.3 (A2), U3.8 (VCC), U5.13 (VDD), U5.28 (AVDD), U6.3 (VIN), U6.7 (SHDN#), U7.5 (VIO), U9.5 (VIN), U$2.P$41 (41), U$2.P$42 (42), X2.39, X2.40, X2.41, X2.42, X2.190, X2.191, X2.192, X2.193, X2.194, X2.197, X2.198, X2.199, X2.200
5V: C25.+, C30.1, U6.2 (VOUT), U7.3 (VDD)
!MCLR: J3.P$6 (6), R4.2, U5.1 (MCLR)
+12V: C1.P$2 (+), U2.1 (VIN), X1.1, X1.9
A: R6.2, U5.2 (AN0/OA2OUT/RA0), U$1.A
ANODE: C23.1, D3.C, U$2.P$3 (3), U$2.P$4 (4)
B: R7.2, U5.3 (AN1/C2IN1+/RA1), U$1.B
B0: U$2.P$12 (12), X2.15
B1: U$2.P$13 (13), X2.17
B2: U$2.P$14 (14), X2.21
B3: U$2.P$15 (15), X2.23
B4: U$2.P$16 (16), X2.27
B5: U$2.P$17 (17), X2.29
B6: U$2.P$18 (18), X2.33
B7: U$2.P$19 (19), X2.35
BRIGHT_PWM: U9.4 (EN), X2.72
C1RX: U5.24 (RPI45/CTPLS/RB13), U7.4 (RXD)
C1TX: U5.11 (RP36/RB4), U7.1 (TXD)
CANH: U7.7 (CANH), X1.4, X1.7
CANL: U7.6 (CANL), X1.2, X1.8
CATHODE: R21.2, U9.3 (FB), U$2.P$1 (1), U$2.P$2 (2)
D+: U$4.3 (D+), X2.165
DCLK: U$2.P$38 (38), X2.3
DEN: U$2.P$52 (52), X2.5
DM: U$4.2 (D-), X2.167
EBRST: U$2.P$8 (8), X2.76
EMC_DISABLE_N: U5.21 (TDO/RP42/RB10), X2.2
EMC_EN_N1V8: U5.22 (TDI/RP43/RB11), X2.90
G0: U$2.P$20 (20), X2.45
G1: U$2.P$21 (21), X2.47
G2: U$2.P$22 (22), X2.51
G3: U$2.P$23 (23), X2.53
G4: U$2.P$24 (24), X2.57
G5: U$2.P$25 (25), X2.59
G6: U$2.P$26 (26), X2.63
G7: U$2.P$27 (27), X2.65
GND: C1.P$1 (-), C2.C (-), C3.2, C9.-, C10.-, C17.2, C18.2, C19.2, C20.2, C21.2, C23.2, C25.-, C26.-, C30.2, D2.A, J1.2, J3.P$4 (4), J4.2, R8.2, R9.2, R21.1, S1.B2 (2), U1.1 (ADJ), U2.3 (GND), U2.5 (~ON/OFF), U2.6 (GND_2), U3.1 (A0), U3.2 (A1), U3.4 (VSS), U3.7 (WP), U5.8 (VSS), U5.19 (VSS), U5.27 (AVSS), U6.4 (GND), U6.8 (SELECT), U7.2 (VSS), U9.2 (GND), U$1.C, U$1.E, U$1.M1 (GND), U$1.M2 (GND), U$1.M3 (GND), U$1.M4 (GND), U$1.M5 (GND), U$1.M6 (GND), U$2.MNT1 (MNT), U$2.MNT2 (MNT), U$2.P$53 (53), U$2.P$54 (54), U$4.5 (GND), U$4.P$6 (SHIELD), U$4.P$7 (SHIELD), U$6.P$4 (4), U$6.P$7 (7), X1.3, X1.5, X1.6, X1.G1, X1.G2, X2.1, X2.7, X2.8, X2.14, X2.19, X2.20, X2.25, X2.26, X2.31, X2.32, X2.37, X2.38, X2.43, X2.44, X2.49, X2.50, X2.55, X2.56, X2.61, X2.62, X2.67, X2.68, X2.73, X2.74, X2.79, X2.80, X2.85, X2.86, X2.91, X2.92, X2.97, X2.98, X2.103, X2.104, X2.109, X2.110, X2.115, X2.116, X2.121, X2.122, X2.127, X2.133, X2.134, X2.139, X2.140, X2.145, X2.146, X2.151, X2.152, X2.157, X2.163, X2.164, X2.168, X2.169, X2.170, X2.181, X2.182, X2.187, X2.188, X2.195, X2.196
HSYNC: U$2.P$36 (36), X2.11
unnamed: J1.1, U5.18 (TMS/ASDA1/RP4/RB9)
unnamed: D2.C, L3.P$1 (1), U2.2 (OUT)
unnamed: C19.1, Q3.2, U5.9 (OSC1/CLKI/RA2)
unnamed: C10.+, U5.20 (VCAP)
unnamed: C24.-, U6.5 (C-)
unnamed: C24.+, U6.6 (C+)
unnamed: D3.A, L1.2, U9.1 (SW)
unnamed: C20.1, Q3.1, U5.10 (OSC2/CLKO/RA3)
PGC: J3.P$2 (2), U5.6 (PGEC1/AN4/C1IN1+/RPI34/RB2)
PGD: J3.P$3 (3), U5.7 (PGED1/AN5/C1IN1-/RP35/RB3)
R0: U$2.P$28 (28), X2.69
R1: U$2.P$29 (29), X2.71
R2: U$2.P$30 (30), X2.75
R3: U$2.P$31 (31), X2.77
R4: U$2.P$32 (32), X2.81
R5: U$2.P$33 (33), X2.83
R6: U$2.P$34 (34), X2.87
R7: U$2.P$35 (35), X2.89
RESET#: J4.1, U5.23 (RPI44/RB12)
RUN: U$6.P$1 (1), X2.177
RXD0: U5.17 (TCK/CVREF10/ASCL1/RP40/T4CK/RB8), X2.60
SCL: R1.1, U3.6 (SCL), U5.15 (RGEC2/ASCL2/RP38/RB6)
SDA: R5.1, U3.5 (SDA), U5.14 (PGED2/ASDA2/RP37/RB5)
SPCK: R8.1, U$2.P$10 (10), X2.84
SPDA: R9.1, U$2.P$11 (11), X2.82
SPENB: U$2.P$9 (9), X2.78
SW1: R3.2, U5.4 (PGED3/VREF-/AN2/C2IN1-/SS1/RPI32/CTED2/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), U$1.D
SW2: R2.1, S1.A2 (1), U5.5 (PGEC3/VREF+/AN3/OA1OUT/RPI33/CTEDRB1)
TXD0: U5.26 (RPI47/T5CK/RB15), X2.58
VBUS: U$4.1 (VBUS)
VC_TCK: U$6.P$8 (8), X2.180
VC_TDI: U$6.P$3 (3), X2.174
VC_TDO: U$6.P$5 (5), X2.178
VC_TMS: U$6.P$6 (6), X2.176
VC_TRST_N: U5.12 (CVREF20/RP20/T1CK/RA4), U$6.P$2 (2), X2.172
VSYNC: U$2.P$37 (37), X2.9

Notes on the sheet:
TFT backlight connector

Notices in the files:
embedded/raspberry-pi/1.0/pihat.brd:
Raspberry Pi-CAN 1.0 (c) 2016
pic/ahrs/4.0/ahrs.brd:
(C) 2017 Kotuku Aerospace
pic/edu/4.4/edu.brd:
(C) 2016, 2017 Kotuku Aerospace Ltd
pic/pihat/1.4/pihat.brd:
Pi-CAN 1.4 (c) 2017
parts and their libraries:
SparkFun-Passives: Licensing: Creative Commons ShareAlike 4.0 International - https://creativecommons.org/licenses/by-sa/4.0
